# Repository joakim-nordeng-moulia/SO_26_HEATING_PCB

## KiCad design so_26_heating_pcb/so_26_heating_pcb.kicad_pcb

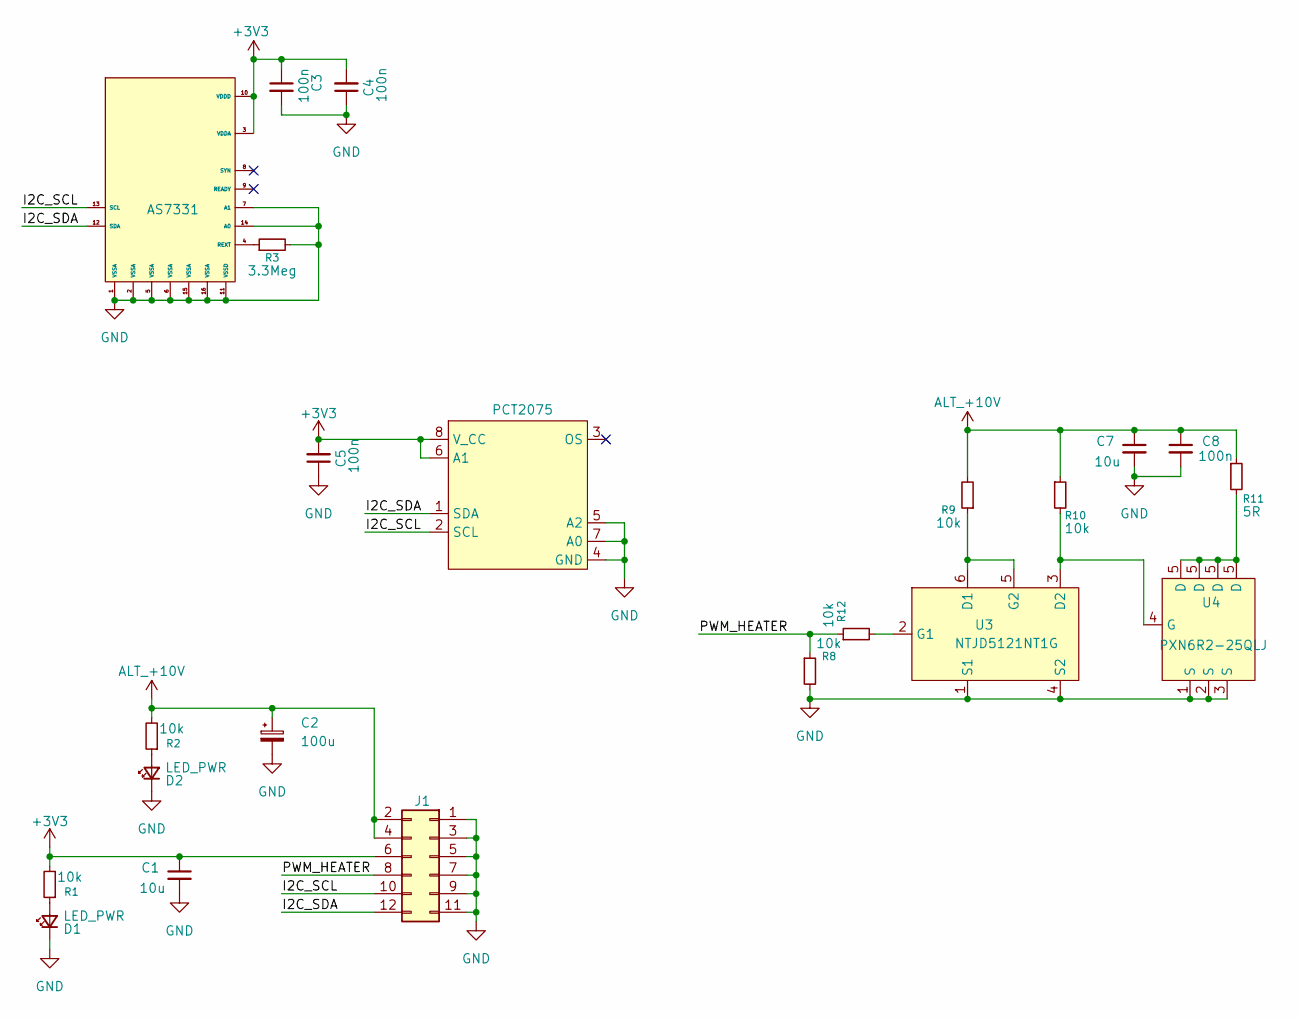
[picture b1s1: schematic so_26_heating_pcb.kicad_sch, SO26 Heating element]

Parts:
C1, C7: 10u; C_1206_3216Metric_Pad1.33x1.80mm_HandSolder
C2: 100u; CP_Radial_D6.3mm_P2.50mm
C3, C4, C5, C8: 100n; C_0805_2012Metric_Pad1.18x1.45mm_HandSolder
D1, D2: LED_PWR; LED_0805_2012Metric_Pad1.15x1.40mm_HandSolder
J1: Conn_02x06_Odd_Even; PinSocket_2x06_P2.54mm_Vertical
R1, R2, R8, R9, R10, R12: 10k; R_0805_2012Metric_Pad1.20x1.40mm_HandSolder
R3: 3.3Meg; R_0805_2012Metric_Pad1.20x1.40mm_HandSolder
R11: 5R; R_Power_Block_27x17_Pxx
U1: AS7331; UV_sensor
U2: PCT2075; TSSOP-8_3x3mm_P0.65mm
U3: NTJD5121NT1G; SOT-363_SC-70-6_Handsoldering
U4: PXN6R2-25QLJ; LFPAK33

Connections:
+3V3: C1.1, C3.1, C4.2, C5.2, J1.6, R1.2, U1.3 (VDDA), U1.10 (VDDD), U2.6 (A1), U2.8 (V_CC)
/I2C_SCL: J1.10, U1.13 (SCL), U2.2 (SCL)
/I2C_SDA: J1.12, U1.12 (SDA), U2.1 (SDA)
/PWM_HEATER: J1.8, R8.1, R12.1
ALT_+10V: C2.1, C7.1, C8.1, J1.2, J1.4, R2.2, R9.2, R10.1, R11.1
GND: C1.2, C2.2, C3.2, C4.1, C5.1, C7.2, C8.2, D1.1 (K), D2.1 (K), J1.1, J1.3, J1.5, J1.7, J1.9, J1.11, R3.2, R8.2, U1.1 (VSSA), U1.2 (VSSA), U1.5 (VSSA), U1.6 (VSSA), U1.7 (A1), U1.11 (VSSD), U1.14 (A0), U1.15 (VSSA), U1.16 (VSSA), U2.4 (GND), U2.5 (A2), U2.7 (A0), U3.1 (S1), U3.4 (S2), U4.1 (S), U4.2 (S), U4.3 (S)
unnamed: D1.2 (A), R1.1
unnamed: D2.2 (A), R2.1
unnamed: R3.1, U1.4 (REXT)
unnamed: R9.1, U3.5 (G2), U3.6 (D1)
unnamed: R10.2, U3.3 (D2), U4.4 (G)
unnamed: R12.2, U3.2 (G1)
unnamed: R11.2, U4.5 (D)

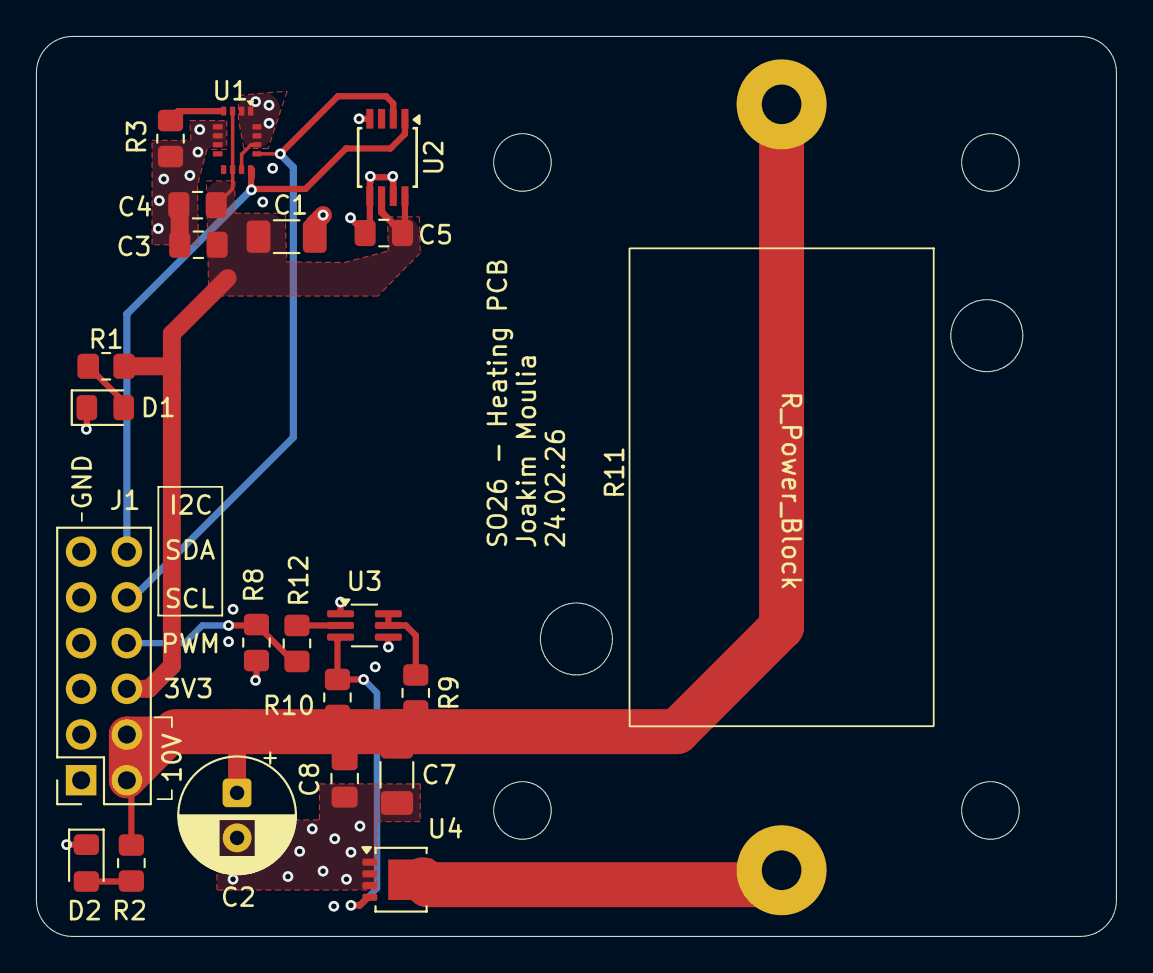
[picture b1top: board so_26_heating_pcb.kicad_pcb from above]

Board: 4 copper layers, 60.0 x 50.0 mm, 22 parts (0 on the bottom side), 13 nets.

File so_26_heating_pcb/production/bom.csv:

Designator,Footprint,Quantity,Value,LCSC Part #
"C1, C7",1206,2,10u,
C2,CP_Radial_D6.3mm_P2.50mm,1,100u,
"C3, C4, C5, C8",0805,4,100n,
"D1, D2",0805,2,LED_PWR,
J1,PinSocket_2x06_P2.54mm_Vertical,1,Conn_02x06_Odd_Even,
"R1, R10, R12, R2, R8, R9",0805,6,10k,
R11,R_Power_Block_27x17_Pxx,1,5R,
R3,0805,1,3.3Meg,
U1,UV_sensor,1,AS7331,
U2,TSSOP-8_3x3mm_P0.65mm,1,PCT2075,
U3,SOT-363_SC-70-6_Handsoldering,1,NTJD5121NT1G,
U4,LFPAK33,1,PXN6R2-25QLJ,

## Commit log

2026-01-28 innit commit
2026-02-04 initial
2026-02-04 UV sensor
2026-02-04 UV symbol og temp og start på heating
2026-02-04 lagt på verdier på resistor
2026-02-06 save
2026-02-06 no connect på OS
2026-02-06 ferdig med første forrsøk på å lage PWM krets
2026-02-08 checked by aj
    schematic:
    - added header
    pcb:
    - added some footprints
2026-02-08 Footprint resistor
2026-02-08 ferdig med footprint resistor
2026-02-08 større pad på uv
2026-02-08 review by aj
2026-02-08 endra med riktig footprint som er assigned
2026-02-08 endret radius på hullene, /2
2026-02-08 forsøkt å legge til mine footprint til project spesific
2026-02-10 Dette er FØR jeg begynner med routing
2026-02-10 Første del av routing før jeg blir litt mer usikker
2026-02-10 reset to commit
2026-02-10 slette alt routing for hånd
2026-02-11 push
2026-02-11 REV 1 finalised
    Schematic done
    PCB done
    ERD/DRC passed
2026-02-11 added via stiching
2026-02-11 added drill origin
2026-02-11 added rev 1 text
2026-02-12 added text
2026-02-24 REV 2
2026-02-24 REV 2.1
